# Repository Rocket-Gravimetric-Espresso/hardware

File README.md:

# Hardware

Custom PCB for the Rocket Gravimetric Espresso project, designed in KiCad 8. The board is powered via 5V USB-C on the XIAO module.

## Components

| Ref | Part | Description |
|-----|------|-------------|
| U1 | [Seeed XIAO nRF52840](https://wiki.seeedstudio.com/XIAO_BLE/) | MCU (I2C, SPI) |
| U2 | [NAU7802SGI](https://www.nuvoton.com/resource-files/NAU7802%20Data%20Sheet%20V1.7.pdf) | 24-bit ADC |
| U3 | [TCK108AF](https://toshiba.semicon-storage.com/info/TCK108AF_datasheet_en_20151229.pdf?did=53240&prodName=TCK108AF) | Load switch for pump control |
| J1 | 4-pin terminal block | [TAL221 500g load cell](https://cdn.sparkfun.com/assets/9/9/a/f/3/TAL221.pdf) connection |
| J3, J4 | 20-pin headers | SPI and I2C breakout for the ([Adafruit 2.8" TFT](https://www.adafruit.com/product/2090)) |

## PCB Layout

## Soldered Board

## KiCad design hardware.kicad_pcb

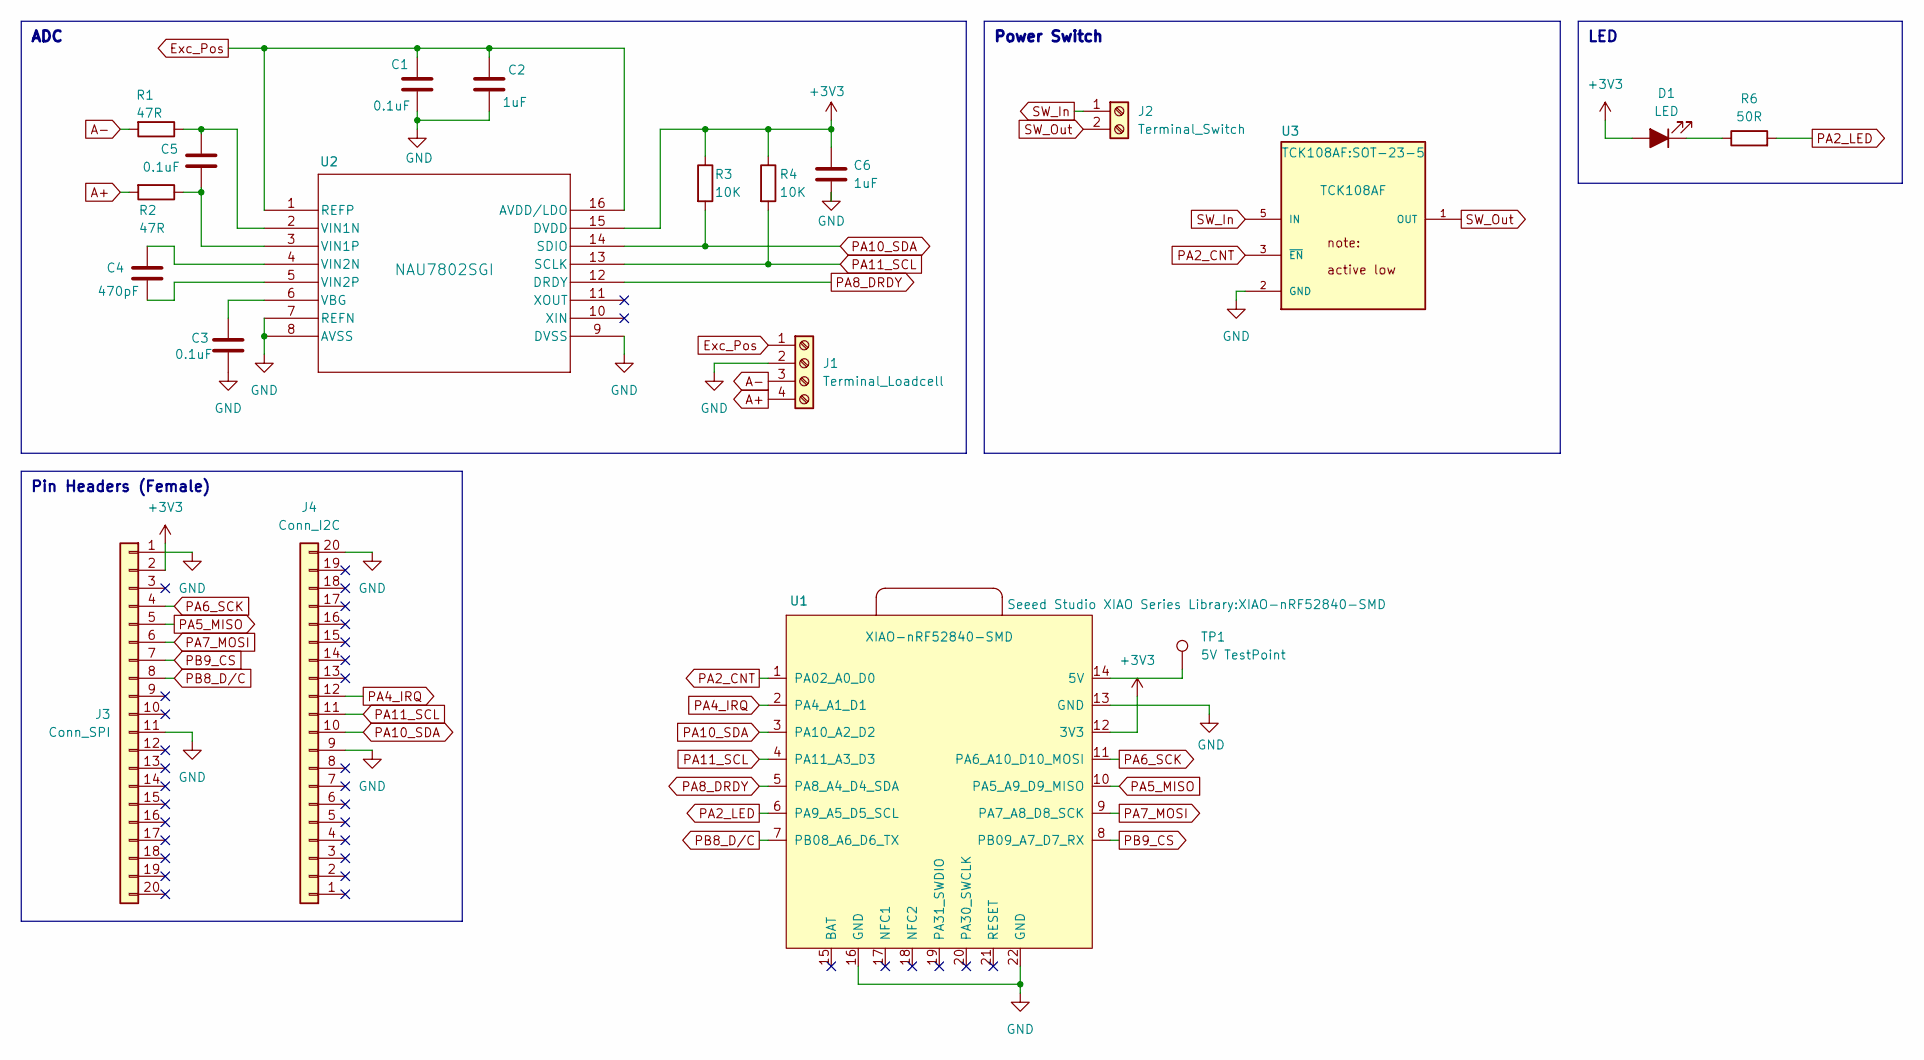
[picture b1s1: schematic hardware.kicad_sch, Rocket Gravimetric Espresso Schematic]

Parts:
C1, C3, C5: 0.1uF; C_1206_3216Metric_Pad1.33x1.80mm_HandSolder
C2, C6: 1uF; C_1206_3216Metric_Pad1.33x1.80mm_HandSolder
C4: 470pF; C_1206_3216Metric_Pad1.33x1.80mm_HandSolder
D1: LED; LED_1206_3216Metric_Pad1.42x1.75mm_HandSolder
J1: Terminal_Loadcell; TerminalBlock_TE_282834-4_1x04_P2.54mm_Horizontal
J2: Terminal_Switch; TerminalBlock_TE_282834-2_1x02_P2.54mm_Horizontal
J3: Conn_SPI; PinSocket_1x20_P2.54mm_Vertical
J4: Conn_I2C; PinSocket_1x20_P2.54mm_Vertical
R1, R2: 47R; R_1206_3216Metric_Pad1.30x1.75mm_HandSolder
R3, R4: 10K; R_1206_3216Metric_Pad1.30x1.75mm_HandSolder
R6: 50R; R_1206_3216Metric_Pad1.30x1.75mm_HandSolder
TP1: 5V TestPoint; TestPoint_Pad_D1.5mm
U1: XIAO-nRF52840-SMD
U2: NAU7802SGI; SOI16_NAU7802SGI_NUV
U3: TCK108AF; SOT-23-5

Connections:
+3V3: C6.1, D1.2 (A), J3.2, R3.1, R4.1, U1.12 (3V3), U2.15 (DVDD)
A+: J1.4, R2.2
A-: J1.3, R1.2
Exc_Pos: C1.1, C2.1, J1.1, U2.1 (REFP), U2.16 (AVDD/LDO)
GND: C1.2, C2.2, C3.2, C6.2, J1.2, J3.1, J3.11, J4.9, J4.20, U1.13 (GND), U1.16 (GND), U1.22 (GND), U2.7 (REFN), U2.8 (AVSS), U2.9 (DVSS), U3.2 (GND)
unnamed: D1.1 (K), R6.1
unnamed: TP1.1, U1.14 (5V)
unnamed: C3.1, U2.6 (VBG)
unnamed: C5.1, R1.1, U2.2 (VIN1N)
unnamed: C5.2, R2.1, U2.3 (VIN1P)
unnamed: C4.1, U2.4 (VIN2N)
unnamed: C4.2, U2.5 (VIN2P)
PA2_CNT: U1.1 (PA02_A0_D0), U3.3 (~EN)
PA2_LED: R6.2, U1.6 (PA9_A5_D5_SCL)
PA4_IRQ: J4.12, U1.2 (PA4_A1_D1)
PA5_MISO: J3.5, U1.10 (PA5_A9_D9_MISO)
PA6_SCK: J3.4, U1.11 (PA6_A10_D10_MOSI)
PA7_MOSI: J3.6, U1.9 (PA7_A8_D8_SCK)
PA8_DRDY: U1.5 (PA8_A4_D4_SDA), U2.12 (DRDY)
PA10_SDA: J4.10, R3.2, U1.3 (PA10_A2_D2), U2.14 (SDIO)
PA11_SCL: J4.11, R4.2, U1.4 (PA11_A3_D3), U2.13 (SCLK)
PB8_D/C: J3.8, U1.7 (PB08_A6_D6_TX)
PB9_CS: J3.7, U1.8 (PB09_A7_D7_RX)
SW_In: J2.1, U3.5 (IN)
SW_Out: J2.2, U3.1 (OUT)

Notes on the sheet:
Power Switch
LED
ADC
Pin Headers (Female)

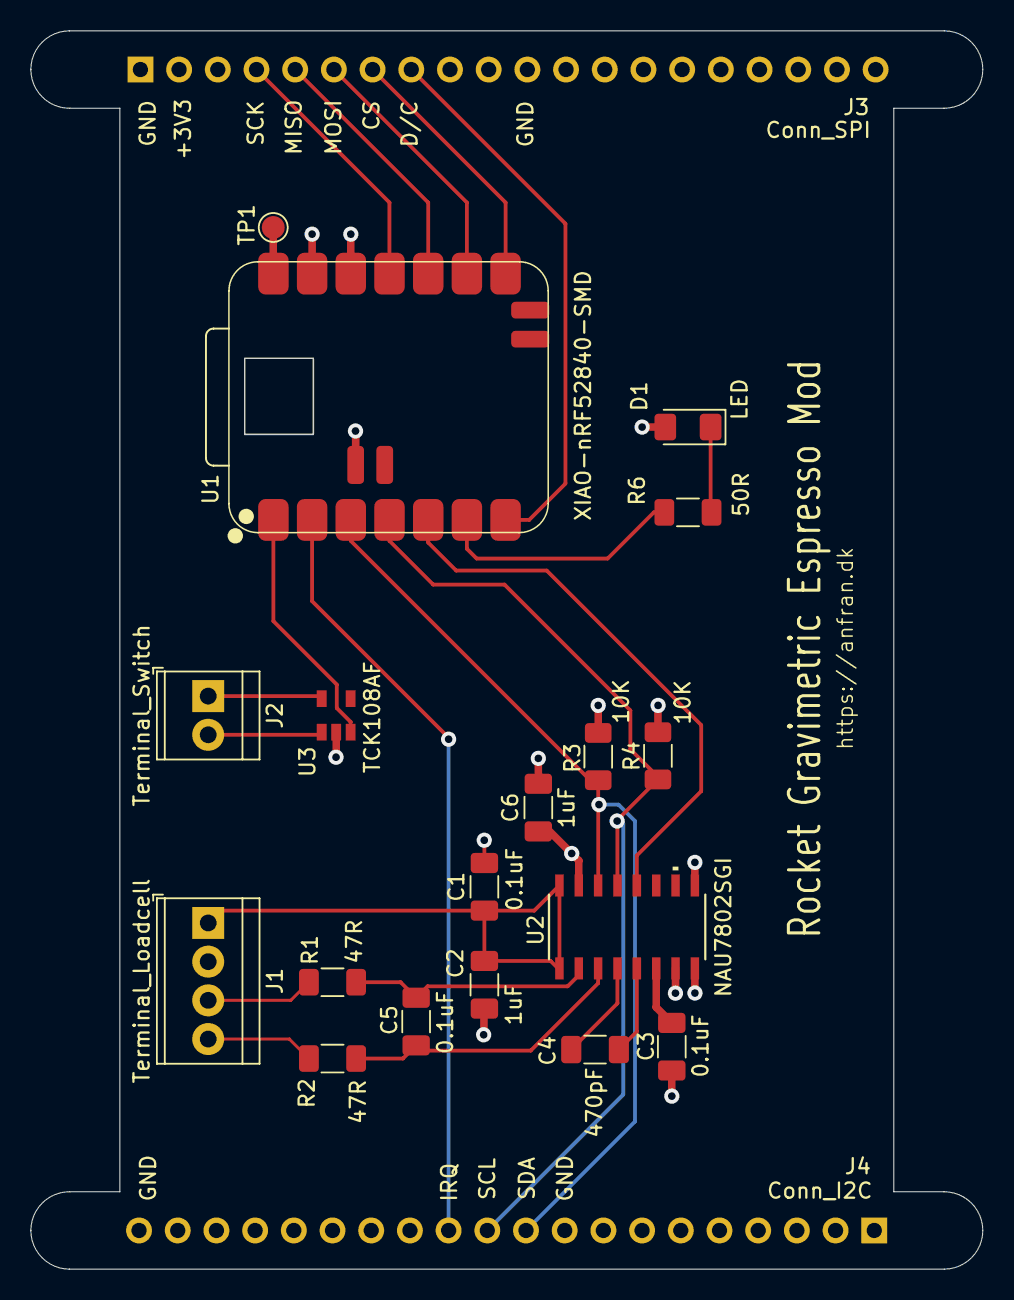
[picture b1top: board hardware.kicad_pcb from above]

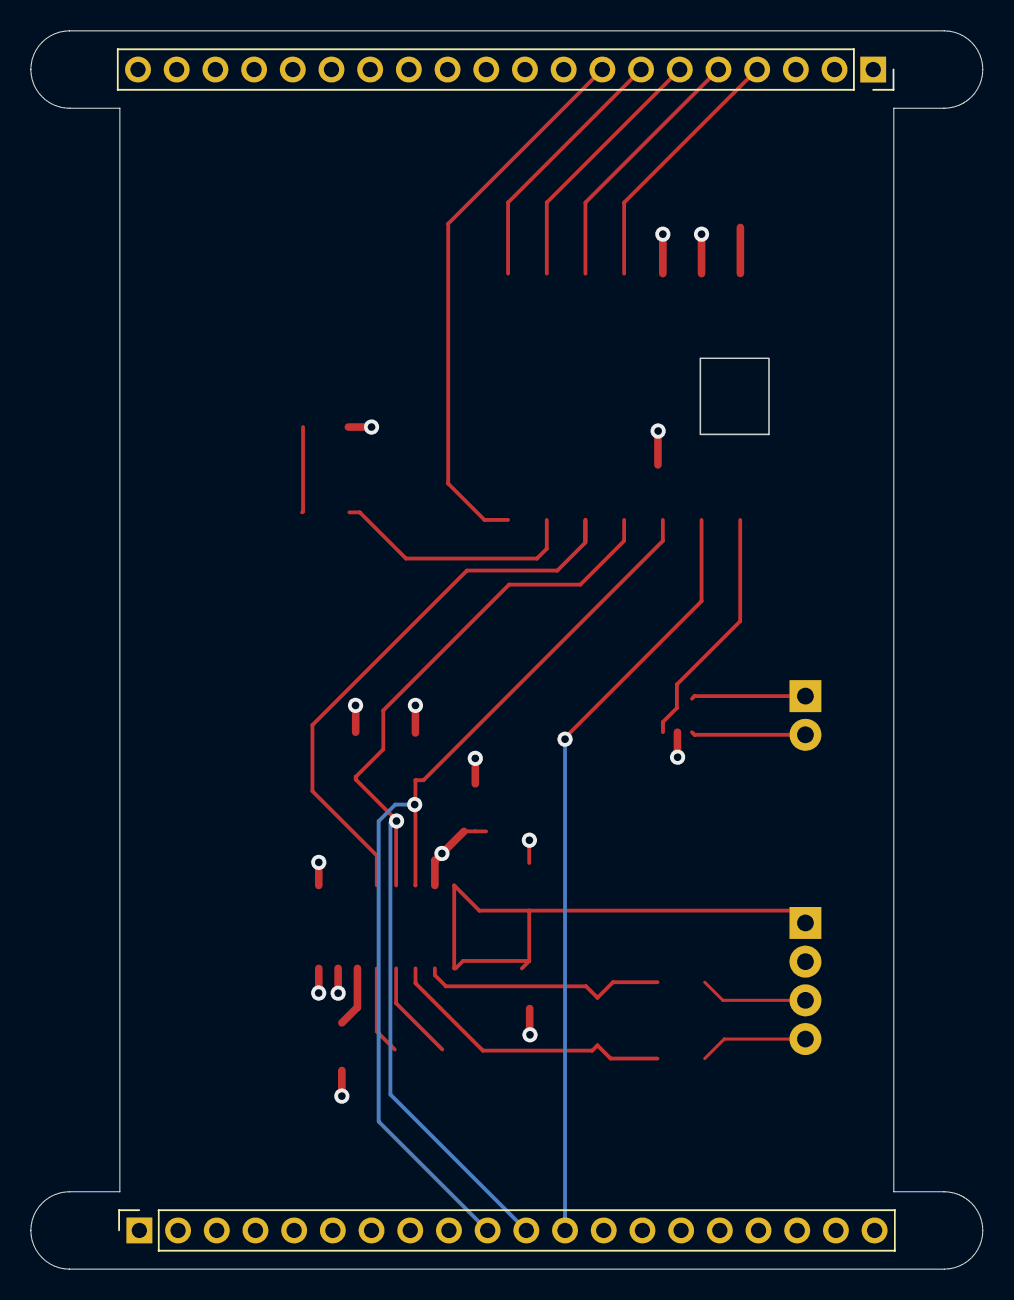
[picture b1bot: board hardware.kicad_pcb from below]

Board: 4 copper layers, 62.4 x 81.2 mm, 20 parts (2 on the bottom side), 25 nets.

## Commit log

2024-11-18 Initial commit: KiCAD project
2024-12-21 schematic v0.1
2025-01-15 finished PCB v0.1
2025-01-26 Added readme
